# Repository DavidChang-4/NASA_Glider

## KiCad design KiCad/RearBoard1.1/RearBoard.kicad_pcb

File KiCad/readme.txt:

BRGR_schematic is old
BRGRavionics2.4.1 is what we made
See the png for how connectorbit and powerpack interface
Midinterface is how the body connects to the avionics

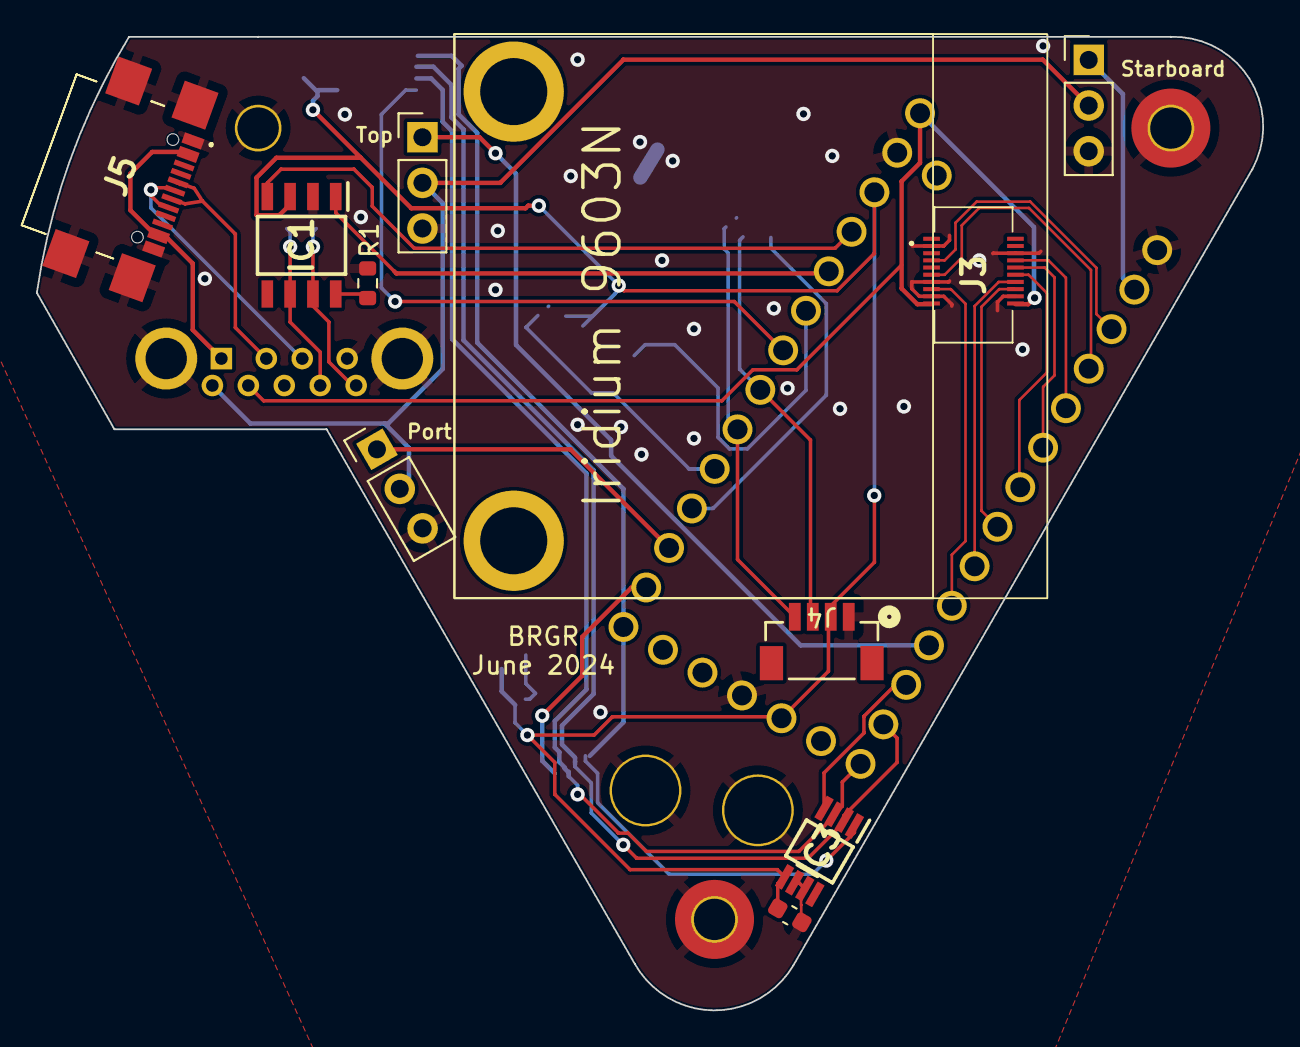
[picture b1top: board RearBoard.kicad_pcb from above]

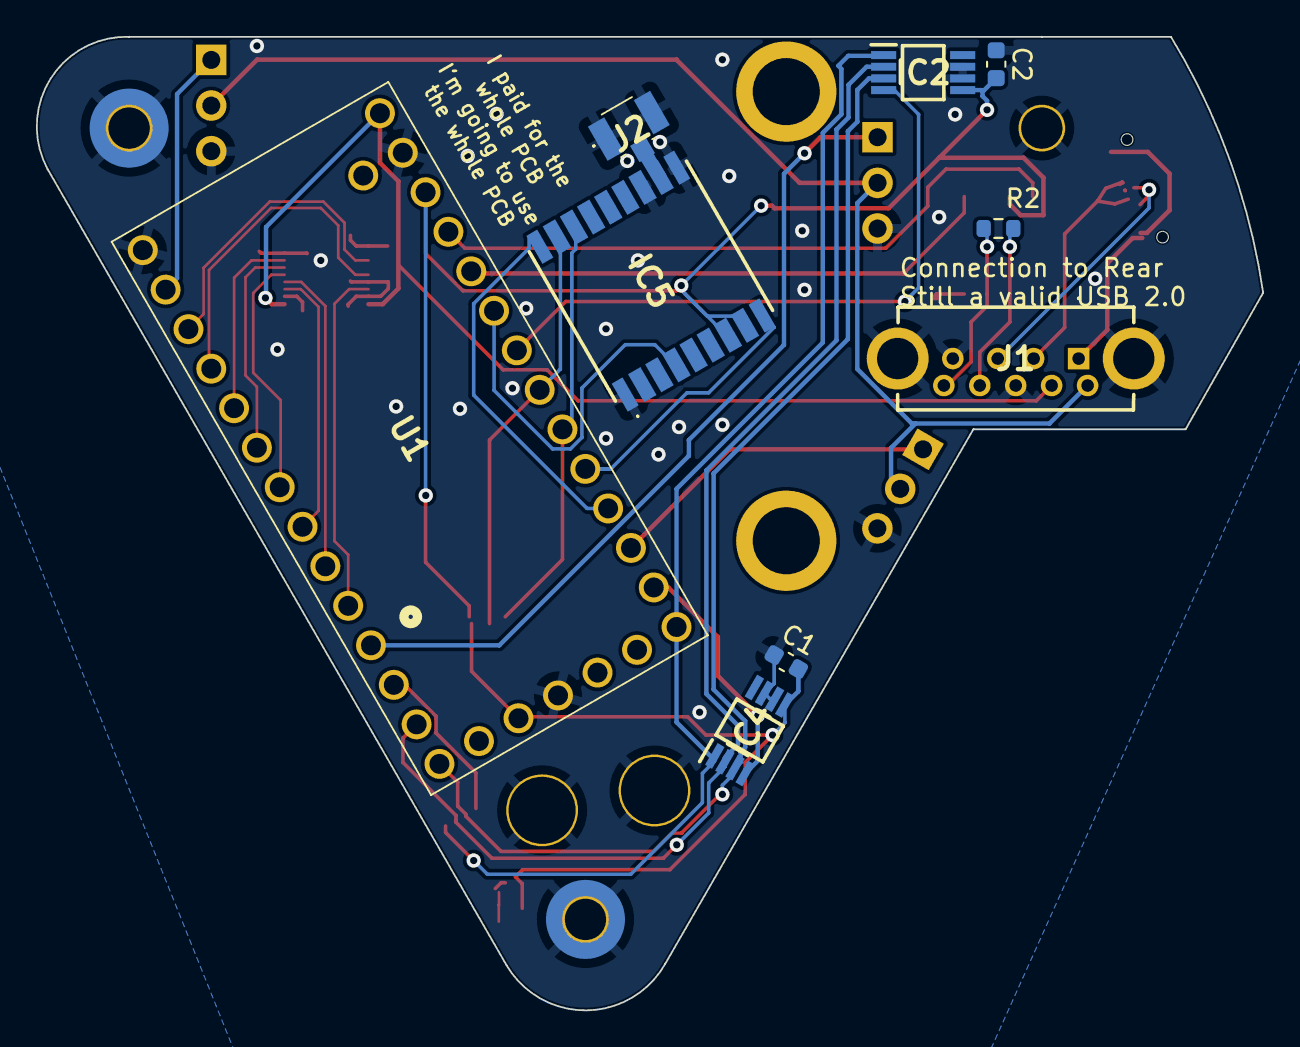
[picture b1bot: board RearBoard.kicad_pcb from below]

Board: 2 copper layers, 68.3 x 54.2 mm, 22 parts (9 on the bottom side), 35 nets.

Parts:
C1, C2, C3: 0.1u; C_0603_1608Metric
H1, H2, H3: MountingHole_Pad; MountingHole_2.2mm_M2_Pad_TopBottom
IC1: SN65HVD230MDREP; SOIC127P600X175-8N
IC2, IC3, IC4: TMAG5170A2QDGKR; SOP65P490X110-8N
IC5: MAX-M10S-00B; MAXM10S00B
J1: SS-52000-004; SS52000004
J2: U.FL-R-SMT_10_; UFLRSMT10
J3: SS4-10-3.00-L-D-K-TR; SS410350LDKTR
J4: BM04B-SRSS-TB; CONN4_BM04B-SRSS_JST
J5: USB4110-GF-A; USB4110GFA
Port: Conn_01x03_Pin; PinHeader_1x03_P2.54mm_Vertical
R1: 10k; R_0603_1608Metric
R2: 120; R_0603_1608Metric
Starboard: Conn_01x03_Pin; PinHeader_1x03_P2.54mm_Vertical
Top: Conn_01x03_Pin; PinHeader_1x03_P2.54mm_Vertical
U1: Teensy4.0; TEENSY40

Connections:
+3.3V: C1.2, C2.2, C3.2, IC1.3 (VCC), IC2.5 (VCC), IC3.5 (VCC), IC4.5 (VCC), IC5.7 (V_IO), IC5.8 (VCC), J4.2, U1.16 (3V3), U1.31 (3V3)
+5V: J1.8 (SSTX-), J3.1, J3.2, U1.33 (VIN)
+BATT: J1.9 (SSTX+), Port.2, Starboard.2, Top.2
/AV USB D+: J1.3 (D+), J5.A6, J5.B6
/AV USB D-: J1.2 (D-), J5.A7, J5.B7
/CAN-H: IC1.7 (CANH), J1.5 (SSRX-), R2.1
/CAN-L: IC1.6 (CANL), J1.6 (SSRX+), R2.2
/CRX: IC1.4 (R), U1.30 (23_A9_CRX1_MCLK1)
/CTS: J3.11, U1.6 (4_BCLK2)
/CTX: IC1.1 (D), U1.29 (22_A8_CTX1)
/DCD: J3.9, U1.7 (5_IN2)
/DSR: J3.10, U1.4 (2_OUT2)
/DTR: J3.14, U1.3 (1_TX1_CTX2_MISO1)
/GPS PPS: IC5.4 (TIMEPULSE), U1.28 (21_A7_RX5_BCLK1)
/GPS Reset: IC5.9 (RESET_N), U1.24 (17_A3_TX4_SDA1)
/GPS Safeboot: IC5.18 (SAFEBOOT_N), U1.23 (16_A2_RX4_SCL1)
/Iridium ON/OFF: J3.5, U1.8 (6_OUT1D)
/Iridium RX: J3.7, U1.9 (7_RX2_OUT1A)
/Iridium TX: J3.6, U1.10 (8_TX2_IN1)
/MISO: IC2.3 (SDO), IC3.3 (SDO), IC4.3 (SDO), U1.14 (12_MISO_MQSL)
/MOSI: IC2.2 (SDI), IC3.2 (SDI), IC4.2 (SDI), U1.13 (11_MOSI_CTX1)
/PortCS: IC3.4 (~CS), U1.12 (10_CS_MQSR)
/PortServo: Port.1, U1.22 (15_A1_RX3_SPDIF_IN)
/RTS: J3.13, U1.5 (3_LRCLK2)
/SCK: IC2.1 (SCK), IC3.1 (SCK), IC4.1 (SCK), U1.20 (13_SCK_CRX1_LED)
/SCL0: IC5.17 (SCL), J4.3, U1.26 (19_A5_SCL0)
/SDA0: IC5.16 (SDA), J4.4, U1.25 (18_A4_SDA0)
/StarboardCS: IC4.4 (~CS), U1.21 (14_A0_TX3_SPDIF_OUT)
/StarboardServo: Starboard.1, U1.2 (0_RX1_CRX2_CS1)
/TopCS: IC2.4 (~CS), U1.27 (20_A6_TX5_LRCLK1)
/TopServo: Top.1, U1.11 (9_OUT1C)
GND: C1.1, C2.1, C3.1, H1.1, H2.1, H3.1, H3.e (1), IC1.2 (GND), IC2.6 (GND), IC2.7 (TEST), IC3.6 (GND), IC3.7 (TEST), IC4.6 (GND), IC4.7 (TEST), IC5.1 (GND_1), IC5.10 (GND_2), IC5.12 (GND_3), J1.4 (GND), J1.7 (GND_DRAIN), J1.MH1, J1.MH2, J2.1 (GND_1), J2.2 (GND_2), J3.3, J3.4, J3.8, J3.15, J3.18, J4.1, J5.A1, J5.A12, J5.B1, J5.B12, J5.MP1, J5.MP2, J5.MP3, J5.MP4, Port.3, R1.2, Starboard.3, Top.3, U1.1 (GND), U1.17 (GND), U1.32 (GND)
unnamed: IC1.8 (RS), R1.1
unnamed: IC5.11 (RF_IN), J2.3 (SIG)
VBUS: J1.1 (VBUS), J5.A4, J5.A9, J5.B4, J5.B9

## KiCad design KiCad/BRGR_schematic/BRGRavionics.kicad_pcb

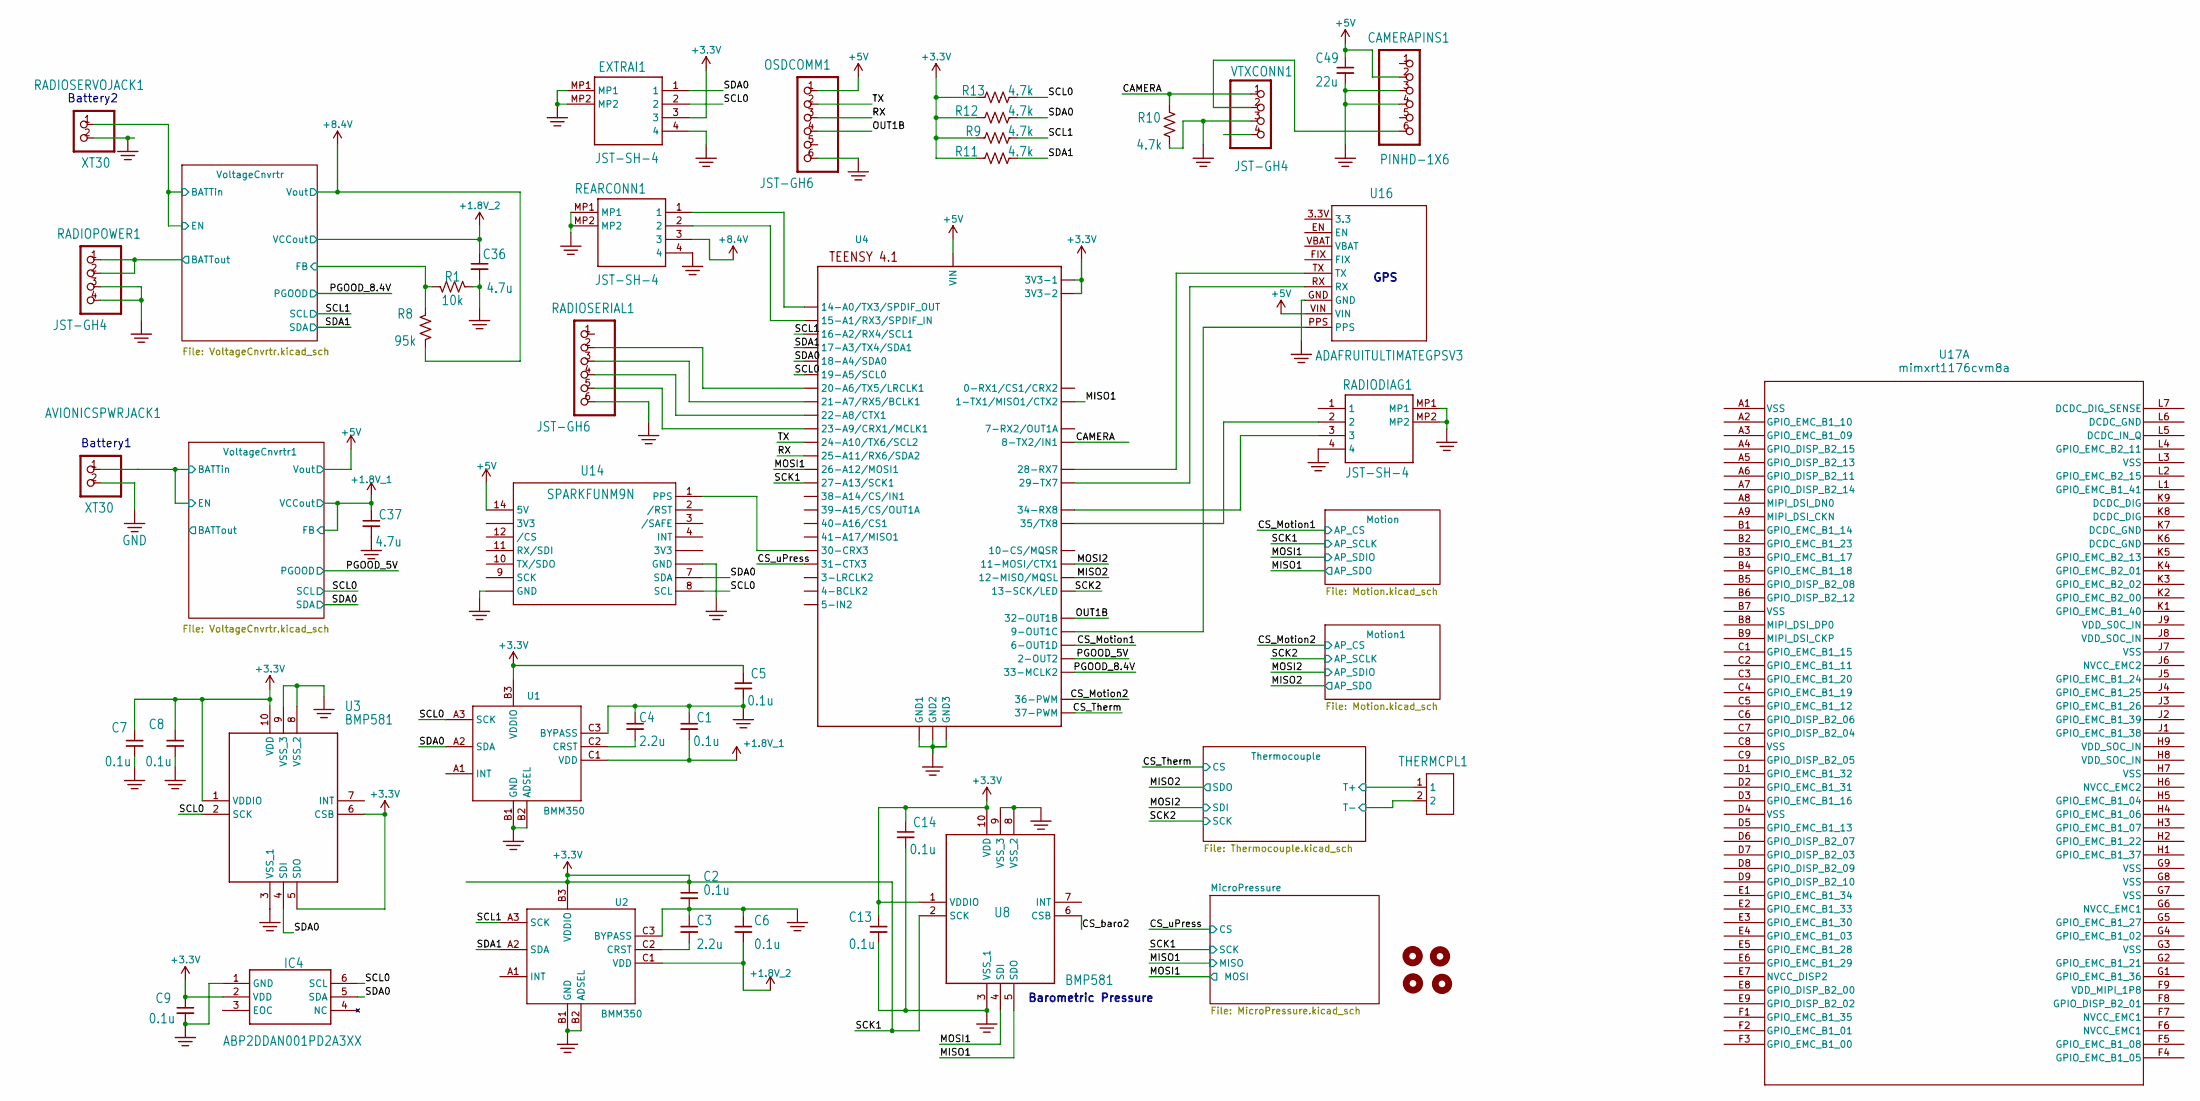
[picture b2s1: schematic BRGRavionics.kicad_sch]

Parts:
AVIONICSPWRJACK1: XT30; AMASS_XT30PW-M
C1, C2, C5, C6, C7, C8, C9, C13, C14: 0.1u; C_0603_1608Metric
C3, C4: 2.2u; C_0603_1608Metric
C36, C37: 4.7u; C_0603_1608Metric
C49: 22u; C_1210_3225Metric
CAMERAPINS1: PINHD-1X6; PinHeader_1x06_P2.54mm_Vertical
EXTRAI1: JST-SH-4; JST_BM04B-SRSS-TB_LF__SN_Mod
H1, H2, H3, H4: MountingHole; MountingHole_70
IC4: ABP2DDAN001PD2A3XX
OSDCOMM1: JST-GH6; JST_SM06B-GHS-TB_LF__SN_Mod
R1: 10k; R_0603_1608Metric
R8: 95k; R_0603_1608Metric
R9, R10, R11, R12, R13: 4.7k; R_0603_1608Metric
RADIODIAG1: JST-SH-4; JST_BM04B-SRSS-TB_LF__SN_Mod
RADIOPOWER1: JST-GH4; JST_SM04B-GHS-TB_LF__SN_-Mod
RADIOSERIAL1: JST-GH6; JST_SM06B-GHS-TB_LF__SN_Mod
RADIOSERVOJACK1: XT30; AMASS_XT30PW-M
REARCONN1: JST-SH-4; JST_SM04B-SRSS-TB(LF)(SN)Mod
THERMCPL1: 2828XX-2282834-2; TerminalBlock_TE_282834-2_1x02_P2.54mm_Horizontal
U1, U2: BMM350; BGA9C40P3X3_128X128X50
U3, U8: BMP581
U4: TEENSY41; MODULE_DEV-16771_v2
U14: SPARKFUNM9N; SparkFun_GPS
U16: ADAFRUITULTIMATEGPSV3; Adafruit_Ultimate_GPS
U17: mimxrt1176cvm8a; 98ASA01216D
VTXCONN1: JST-GH4; JST_BM04B-GHS-TBT(LF)(SN)(N)

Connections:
+5V: C49.1, CAMERAPINS1.2, OSDCOMM1.1, U4.VIN, U14.14 (5V), U16.VIN; also elsewhere on the board
+8V: R8.1, REARCONN1.3; also elsewhere on the board
/CAMERA: R10.2, U4.8 (8-TX2/IN1), VTXCONN1.1
/CS_Motion1: U4.6 (6-OUT1D); also elsewhere on the board
/CS_Motion2: U4.36 (36-PWM); also elsewhere on the board
/CS_Therm: U4.37 (37-PWM); also elsewhere on the board
/CS_uPress: U4.31 (31-CTX3); also elsewhere on the board
/MISO1: U4.1 (1-TX1/MISO1/CTX2), U8.5 (SDO); also elsewhere on the board
/MISO2: U4.12 (12-MISO/MQSL); also elsewhere on the board
/MOSI1: U4.26 (26-A12/MOSI1), U8.4 (SDI); also elsewhere on the board
/MOSI2: U4.11 (11-MOSI/CTX1); also elsewhere on the board
/OUT1B: OSDCOMM1.4, U4.32 (32-OUT1B)
/PGOOD_5V: U4.2 (2-OUT2); also elsewhere on the board
/PGOOD_8.4V: U4.33 (33-MCLK2); also elsewhere on the board
/RX: OSDCOMM1.3, U4.25 (25-A11/RX6/SDA2)
/SCK2: U4.13 (13-SCK/LED); also elsewhere on the board
/SCL0: EXTRAI1.2, R13.1, U1.A3 (SCK), U3.2 (SCK), U4.19 (19-A5/SCL0), U14.8 (SCL); also elsewhere on the board
/SCL1: R9.1, U2.A3 (SCK), U4.16 (16-A2/RX4/SCL1); also elsewhere on the board
/SDA0: EXTRAI1.1, R12.1, U1.A2 (SDA), U3.4 (SDI), U4.18 (18-A4/SDA0), U14.7 (SDA); also elsewhere on the board
/SDA1: R11.1, U2.A2 (SDA), U4.17 (17-A3/TX4/SDA1); also elsewhere on the board
/TX: OSDCOMM1.2, U4.24 (24-A10/TX6/SCL2)
/Thermocouple/T+: THERMCPL1.1; also elsewhere on the board
/Thermocouple/T-: THERMCPL1.2; also elsewhere on the board
/VoltageCnvrtr1/BATTin: AVIONICSPWRJACK1.1 (+); also elsewhere on the board
/VoltageCnvrtr/BATTin: RADIOSERVOJACK1.1 (+); also elsewhere on the board
/VoltageCnvrtr/BATTout: RADIOPOWER1.1, RADIOPOWER1.2; also elsewhere on the board
/VoltageCnvrtr/FB: R1.1, R8.2; also elsewhere on the board
GND: AVIONICSPWRJACK1.2 (-), C1.1, C2.2, C3.1, C4.1, C5.2, C6.1, C7.2, C8.2, C9.2, C13.2, C14.2, C36.2, C37.2, C49.2, CAMERAPINS1.3, CAMERAPINS1.4, EXTRAI1.4, EXTRAI1.MP1, EXTRAI1.MP2, OSDCOMM1.6, R1.2, R10.1, RADIODIAG1.4, RADIODIAG1.MP1, RADIODIAG1.MP2, RADIOPOWER1.3, RADIOPOWER1.4, RADIOSERIAL1.6, RADIOSERVOJACK1.2 (-), REARCONN1.4, REARCONN1.MP1, REARCONN1.MP2, U1.B1 (GND), U1.B2 (ADSEL), U1.C3 (BYPASS), U2.B1 (GND), U2.B2 (ADSEL), U2.C3 (BYPASS), U3.3 (VSS_1), U3.8 (VSS_2), U3.9 (VSS_3), U4.GND1, U4.GND2, U4.GND3, U8.3 (VSS_1), U8.8 (VSS_2), U8.9 (VSS_3), U14.5 (GND), U14.15 (GND), U16.GND, VTXCONN1.3; also elsewhere on the board
unnamed: CAMERAPINS1.6, VTXCONN1.2
unnamed: C4.2, U1.C2 (CRST)
unnamed: C3.2, U2.C2 (CRST)
unnamed: U4.9 (9-OUT1C), U16.PPS
unnamed: REARCONN1.1, U4.14 (14-A0/TX3/SPDIF_OUT)
unnamed: REARCONN1.2, U4.15 (15-A1/RX3/SPDIF_IN)
unnamed: RADIOSERIAL1.2, U4.20 (20-A6/TX5/LRCLK1)
unnamed: RADIOSERIAL1.3, U4.21 (21-A7/RX5/BCLK1)
unnamed: RADIOSERIAL1.4, U4.22 (22-A8/CTX1)
unnamed: RADIOSERIAL1.5, U4.23 (23-A9/CRX1/MCLK1)
unnamed: U4.28 (28-RX7), U16.TX
unnamed: U4.29 (29-TX7), U16.RX
unnamed: RADIODIAG1.3, U4.34 (34-RX8)
unnamed: RADIODIAG1.2, U4.35 (35/TX8)
unnamed: U4.30 (30-CRX3), U14.1 (PPS)

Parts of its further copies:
U5: ABP2DDAN001PD2A3XX

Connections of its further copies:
/SCL0: U5.6 (SCL); also elsewhere on the board
/SDA0: U5.5 (SDA); also elsewhere on the board
GND: U5.1 (GND); also elsewhere on the board

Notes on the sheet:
Barometric Pressure
GPS
Battery2
Battery1

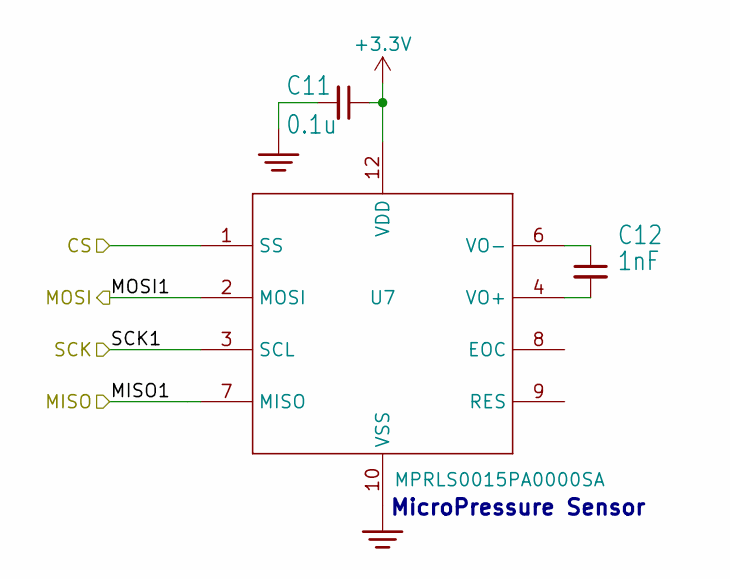
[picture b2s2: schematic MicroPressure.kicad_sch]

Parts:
C11: 0.1u; C_0603_1608Metric
C12: 1nF; C_0603_1608Metric
U7: MPRLS0015PA0000SA

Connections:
/CS_uPress: U7.1 (SS); also elsewhere on the board
/MISO1: U7.7 (MISO); also elsewhere on the board
/MOSI1: U7.2 (MOSI); also elsewhere on the board
GND: C11.2, U7.10 (VSS); also elsewhere on the board
unnamed: C12.2, U7.4 (VO+)
unnamed: C12.1, U7.6 (VO-)

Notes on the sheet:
MicroPressure Sensor

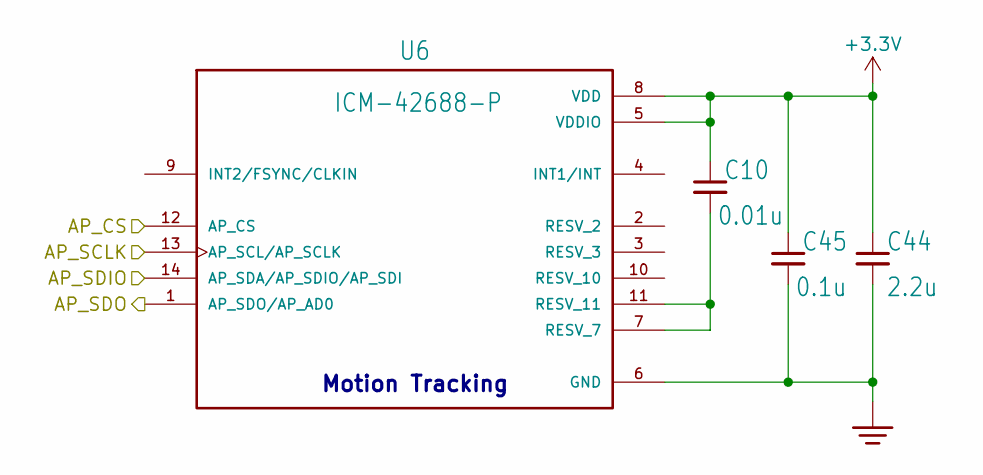
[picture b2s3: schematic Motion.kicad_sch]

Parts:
C10: 0.01u; C_0603_1608Metric
C44: 2.2u; C_0603_1608Metric
C45: 0.1u; C_0603_1608Metric
U6: ICM-42688-P; PQFN50P300X250X97-14N; PARTREV 1.2; DigiKey_Part_Number 1428-ICM-42688-PTR-ND

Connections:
/CS_Motion1: U6.12 (AP_CS); also elsewhere on the board
/MISO1: U6.1 (AP_SDO/AP_AD0); also elsewhere on the board
/MOSI1: U6.14 (AP_SDA/AP_SDIO/AP_SDI); also elsewhere on the board
GND: C44.2, C45.2, U6.6 (GND); also elsewhere on the board
unnamed: C10.2, U6.7 (RESV_7), U6.11 (RESV_11)

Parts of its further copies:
C46: 0.01u; C_0603_1608Metric
C47: 0.1u; C_0603_1608Metric
C48: 2.2u; C_0603_1608Metric
U15: ICM-42688-P; PQFN50P300X250X97-14N; PARTREV 1.2; DigiKey_Part_Number 1428-ICM-42688-PTR-ND

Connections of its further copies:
/CS_Motion2: U15.12 (AP_CS); also elsewhere on the board
/MISO2: U15.1 (AP_SDO/AP_AD0); also elsewhere on the board
/MOSI2: U15.14 (AP_SDA/AP_SDIO/AP_SDI); also elsewhere on the board
/SCK2: U15.13 (AP_SCL/AP_SCLK); also elsewhere on the board
GND: C47.2, C48.2, U15.6 (GND); also elsewhere on the board
unnamed: C46.2, U15.7 (RESV_7), U15.11 (RESV_11)

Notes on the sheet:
Motion Tracking

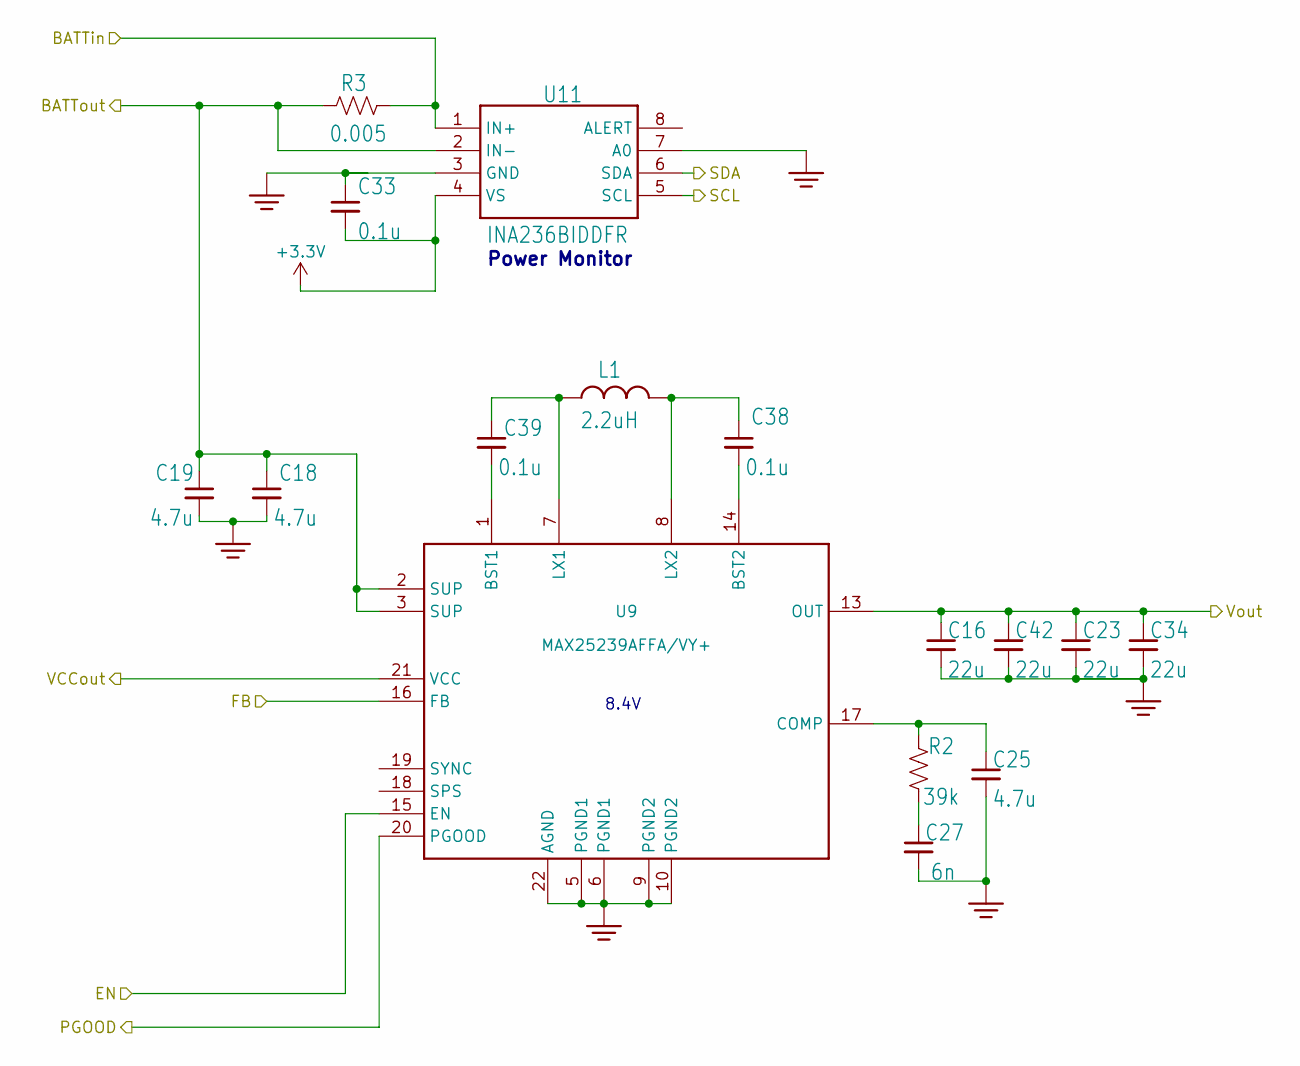
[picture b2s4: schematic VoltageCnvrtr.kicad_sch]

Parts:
C16, C23, C34, C42: 22u; C_1210_3225Metric
C18, C19: 4.7u; C_1206_3216Metric
C25: 4.7u; C_0603_1608Metric
C27: 6n; C_0603_1608Metric
C33, C38, C39: 0.1u; C_0603_1608Metric
L1: 2.2uH; L_Bourns_SRP3020CC
R2: 39k; R_0603_1608Metric
R3: 0.005; RESC6432X55N
U9: MAX25239AFFA/VY+; MAX25239
U11: INA236BIDDFR; SOT23-THN-8

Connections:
+8V: C16.1, C23.1, C34.1, C42.1, U9.12 (OUT), U9.13 (OUT); also elsewhere on the board
/PGOOD_8.4V: U9.20 (PGOOD); also elsewhere on the board
/SCL1: U11.5 (SCL); also elsewhere on the board
/SDA1: U11.6 (SDA); also elsewhere on the board
/VoltageCnvrtr/BATTin: R3.1, U9.15 (EN), U11.1 (IN+); also elsewhere on the board
/VoltageCnvrtr/BATTout: C18.1, C19.1, R3.2, U9.2 (SUP), U9.3 (SUP), U11.2 (IN-); also elsewhere on the board
/VoltageCnvrtr/FB: U9.16 (FB); also elsewhere on the board
GND: C16.2, C18.2, C19.2, C23.2, C25.2, C27.2, C33.1, C34.2, C42.2, U9.5 (PGND1), U9.6 (PGND1), U9.9 (PGND2), U9.10 (PGND2), U9.22 (AGND), U11.3 (GND), U11.7 (A0); also elsewhere on the board
unnamed: C27.1, R2.2
unnamed: C39.2, U9.1 (BST1)
unnamed: C38.2, U9.14 (BST2)
unnamed: C25.1, R2.1, U9.17 (COMP)
unnamed: C39.1, L1.1, U9.7 (LX1)
unnamed: C38.1, L1.2, U9.8 (LX2)

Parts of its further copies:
C17, C24, C35, C43: 22u; C_1210_3225Metric
C20, C21: 4.7u; C_1206_3216Metric
C26: 4.7u; C_0603_1608Metric
C28: 6n; C_0603_1608Metric
C32, C40, C41: 0.1u; C_0603_1608Metric
L2: 2.2uH; L_Bourns_SRP3020CC
R4: 39k; R_0603_1608Metric
R5: 0.005; RESC6432X55N
U10: MAX25239AFFA/VY+; MAX25239
U12: INA236BIDDFR; SOT23-THN-8

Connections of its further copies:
+5V: C17.1, C24.1, C35.1, C43.1, U10.12 (OUT), U10.13 (OUT); also elsewhere on the board
/PGOOD_5V: U10.20 (PGOOD); also elsewhere on the board
/SCL0: U12.5 (SCL); also elsewhere on the board
/SDA0: U12.6 (SDA); also elsewhere on the board
/VoltageCnvrtr1/BATTin: R5.1, U10.15 (EN), U12.1 (IN+); also elsewhere on the board
/VoltageCnvrtr1/BATTout: C20.1, C21.1, R5.2, U10.2 (SUP), U10.3 (SUP), U12.2 (IN-)
GND: C17.2, C20.2, C21.2, C24.2, C26.2, C28.2, C32.1, C35.2, C43.2, U10.5 (PGND1), U10.6 (PGND1), U10.9 (PGND2), U10.10 (PGND2), U10.22 (AGND), U12.3 (GND), U12.7 (A0); also elsewhere on the board
unnamed: C28.1, R4.2
unnamed: C41.2, U10.1 (BST1)
unnamed: C40.2, U10.14 (BST2)
unnamed: C26.1, R4.1, U10.17 (COMP)
unnamed: C41.1, L2.1, U10.7 (LX1)
unnamed: C40.1, L2.2, U10.8 (LX2)

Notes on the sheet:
Power Monitor
8.4V

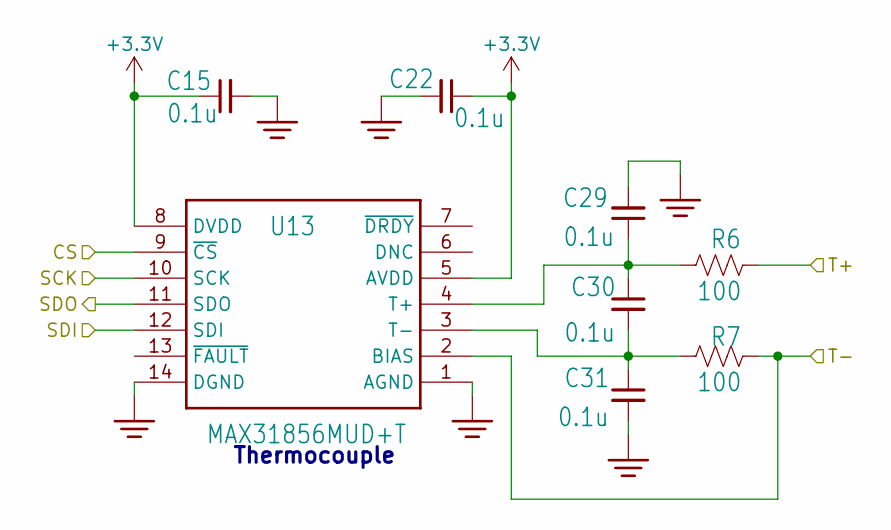
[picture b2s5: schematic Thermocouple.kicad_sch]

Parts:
C15, C22, C29, C30, C31: 0.1u; C_0603_1608Metric
R6, R7: 100; R_0603_1608Metric
U13: MAX31856MUD+T; SOP65P640X110-14N

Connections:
/CS_Therm: U13.9 (~CS); also elsewhere on the board
/MISO2: U13.11 (SDO); also elsewhere on the board
/MOSI2: U13.12 (SDI); also elsewhere on the board
/SCK2: U13.10 (SCK); also elsewhere on the board
/Thermocouple/T+: R6.1; also elsewhere on the board
/Thermocouple/T-: R7.1, U13.2 (BIAS); also elsewhere on the board
GND: C15.2, C22.2, C29.2, C31.2, U13.1 (AGND), U13.14 (DGND); also elsewhere on the board
unnamed: C29.1, C30.1, R6.2, U13.4 (T+)
unnamed: C30.2, C31.1, R7.2, U13.3 (T-)

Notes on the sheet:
Thermocouple

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
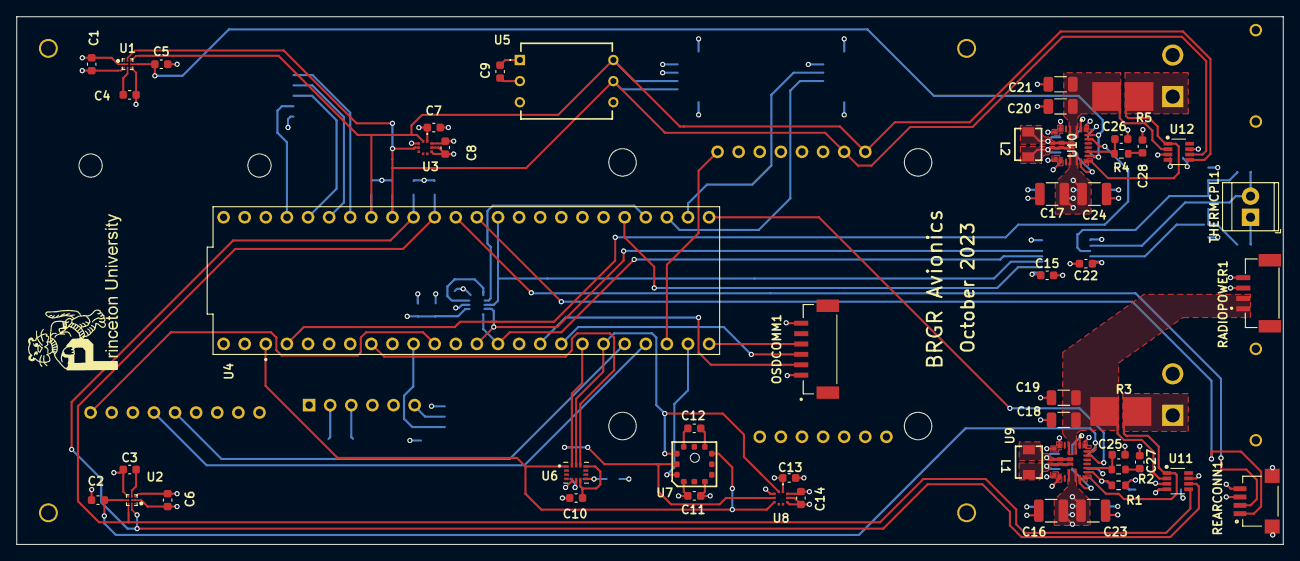
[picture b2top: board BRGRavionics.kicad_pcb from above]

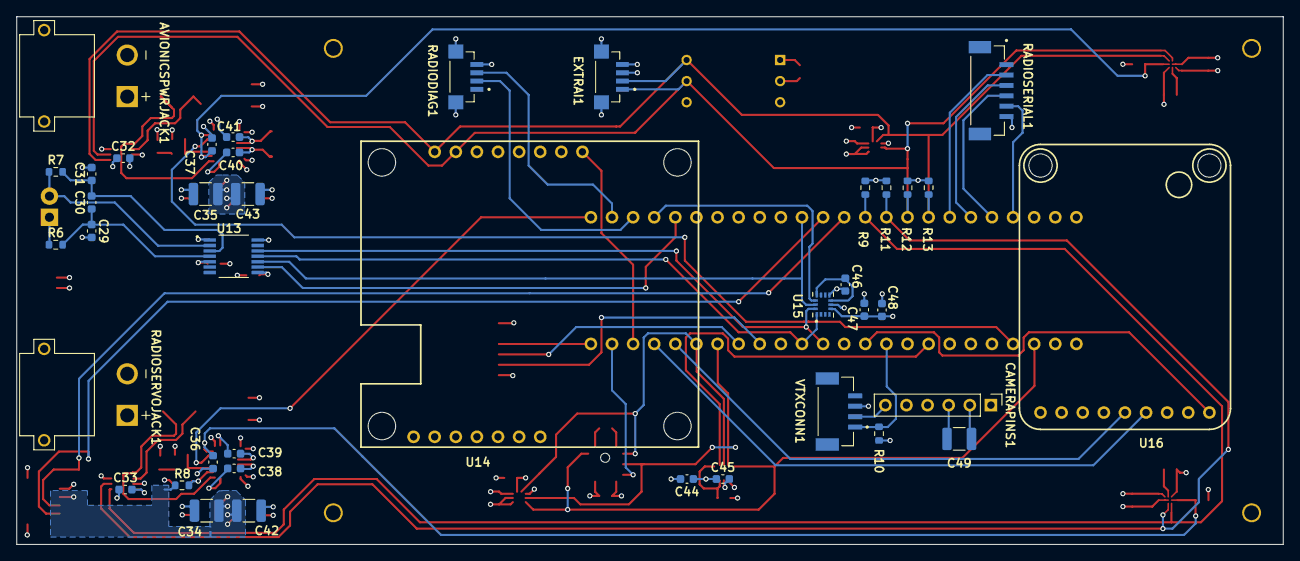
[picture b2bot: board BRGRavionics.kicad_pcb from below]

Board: 4 copper layers, 152.4 x 63.5 mm, 96 parts (40 on the bottom side), 66 nets.

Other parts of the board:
G1: LOGO; t_

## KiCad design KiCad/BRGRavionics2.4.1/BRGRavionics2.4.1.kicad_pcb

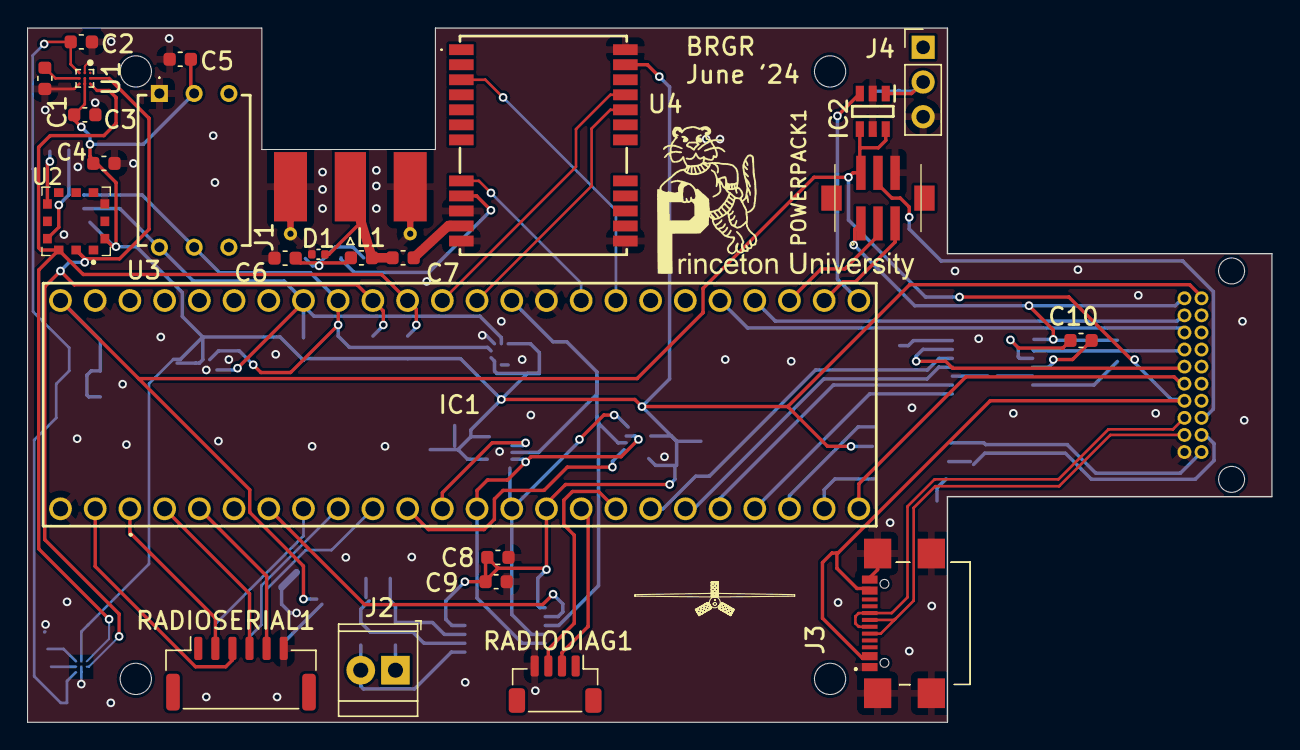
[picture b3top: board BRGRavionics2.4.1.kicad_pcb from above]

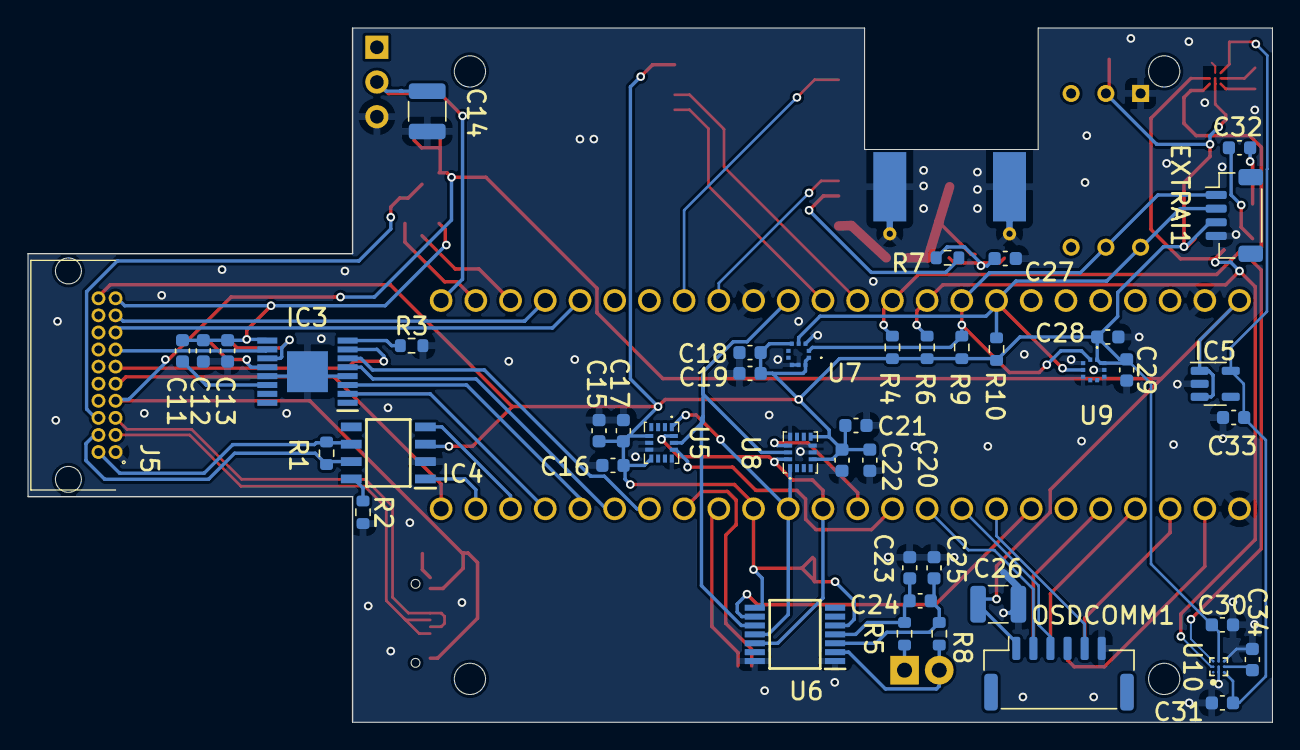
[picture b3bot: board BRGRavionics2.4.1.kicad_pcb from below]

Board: 2 copper layers, 91.1 x 50.8 mm, 76 parts (46 on the bottom side), 65 nets.

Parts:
C1, C16, C22, C34: 2.2u; C_0603_1608Metric
C2, C3, C4, C5, C8, C9, C10, C11, C12, C17, C18, C19, C20, C23, C24, C25, C28, C29, C30, C31, C33: 0.1u; C_0603_1608Metric
C6: 0.1uF; C_0603_1608Metric
C7, C27: 47pF; C_0603_1608Metric
C13: 100u; C_0603_1608Metric
C14, C26: 22u; C_1210_3225Metric
C15, C21: 0.01u; C_0603_1608Metric
C32: 1nF; C_0603_1608Metric
D1: TVS_0402; C_0402_1005Metric
EXTRAI1: JST-SH-4; JST_SH_BM04B-SRSS-TB_1x04-1MP_P1.00mm_Vertical
G1: LOGO; t_
H1, H2, H3, H4: MountingHole; MountingHole_90
IC1: TEENSY_4.1; TEENSY41
IC2: AP22913W6-7; SOT95P285X140-6N
IC3: DRV8800PWPR; SOP65P640X120-17N
IC4: SN65HVD230MDREP; SOIC127P600X175-8N
IC5: ADP151WAUJZ-1.8-R7; TSOT-23-5
J1: SMA_EdgeMount; SMA_Molex_73251-1153_EdgeMount_Horizontal
J2: Thermocouple Terminal; TerminalBlock_TE_282834-2_1x02_P2.54mm_Horizontal
J3: USB4110-GF-A; USB4110GFA
J4: Camera Pins; PinHeader_1x03_P2.54mm_Vertical
J5: G125-MH12005L5P
L1: 33nH; C_0603_1608Metric
OSDCOMM1: JST-GH6; JST_GH_SM06B-GHS-TB_1x06-1MP_P1.25mm_Horizontal
POWERPACK1: G125-MS10605L3P
R1: 120; R_0603_1608Metric
R2: 10k; R_0603_1608Metric
R3: 0.2; R_0603_1608Metric
R4, R6, R9, R10: 4.7k; R_0603_1608Metric
R5, R8: 100; R_0603_1608Metric
R7: 10; R_0603_1608Metric
RADIODIAG1: JST-SH-4; JST_SH_BM04B-SRSS-TB_1x04-1MP_P1.00mm_Vertical
RADIOSERIAL1: JST-GH6; JST_GH_SM06B-GHS-TB_1x06-1MP_P1.25mm_Horizontal
U1, U10: BMM350; BGA9C40P3X3_128X128X50
U2: MPRLS0015PA0000SA; MPRLS0025PA00001A
U3: ABP2DDAN001PD2A3XX; ABP2DANT001BA2A3XX
U4: NEO-M10N; NEOM9N00B
U5, U8: ICM-42688-P; IIM42352
U6: MAX31856MUD+T; SOP65P640X110-14N
U7, U9: BMP581

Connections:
+1V8_1: C2.2, C31.2, C33.1, IC5.5 (VOUT), U1.C1 (VDD), U10.C1 (VDD)
+3.3V: C3.1, C4.1, C5.1, C8.1, C9.1, C15.1, C16.1, C17.1, C18.1, C19.1, C20.1, C21.1, C22.1, C28.1, C29.1, C30.1, EXTRAI1.3, IC1.42 (3.3V_1), IC4.3 (VCC), J5.20, R4.2, R6.2, R9.2, R10.2, U1.B2 (ADSEL), U1.B3 (VDDIO), U2.12 (VDD), U3.2 (VDD), U4.23 (VCC), U5.5 (VDDIO), U5.8 (VDD), U6.5 (AVDD), U6.8 (DVDD), U7.1 (VDDIO), U7.5 (SDO), U7.10 (VDD), U8.5 (VDDIO), U8.8 (VDD), U9.1 (VDDIO), U9.10 (VDD), U10.B3 (VDDIO)
+5V: C26.1, IC1.55 (VIN_(3.6_TO_5.5_VOLTS)), IC2.4 (VIN_1), IC2.6 (VIN_2), IC5.1 (VIN), IC5.3 (EN), J3.A4, J3.A9, J3.B4, J3.B9, J5.4, OSDCOMM1.1, POWERPACK1.4
+BATT: C11.2, C12.1, C13.1, IC3.9 (VBB), J5.10, POWERPACK1.1
/CAN-H: IC4.7 (CANH), J5.12, R1.1
/CAN-L: IC4.6 (CANL), J5.11, R1.2
/CRX: IC1.30 (CRX3), IC4.4 (R)
/CS_Motion1: IC1.9 (OUT1C), U5.12 (AP_CS)
/CS_Motion2: IC1.10 (CS_1), U8.12 (AP_CS)
/CS_Therm: IC1.5 (IN2), U6.9 (~CS)
/CTX: IC1.31 (CTX3), IC4.1 (D)
/CameraON: IC1.33 (MCLK2), IC2.3 (ON)
/Encoder A: IC1.37 (CS_3), J5.8
/Encoder B: IC1.36 (CS_2), J5.9
/GPS Pulse: IC1.40 (A16), U4.3 (TIME_PULSE)
/GPS RESET: IC1.41 (A17), U4.8 (RESET_N)
/GPS RX: IC1.14 (A0), U4.20 (TXD)
/GPS TX: IC1.15 (A1), U4.21 (RXD)
/Limit Switch: IC1.32 (OUT1B), J5.5
/M+: IC3.7 (OUT+), J5.6
/M-: IC3.10 (OUT-), J5.7
/MISO1: IC1.12 (MISO), U5.1 (AP_SDO/AP_AD0), U6.11 (SDO), U8.1 (AP_SDO/AP_AD0)
/MOSI1: IC1.11 (MOSI), U5.14 (AP_SDA/AP_SDIO/AP_SDI), U6.12 (SDI), U8.14 (AP_SDA/AP_SDIO/AP_SDI)
/Motor Enable: IC1.28 (RX7), IC3.3 (PHASE)
/Motor Mode: IC1.29 (TX7), IC3.2 (MODE)
/Motor Phase: IC1.26 (A12), IC3.6 (ENABLE)
/Motor Sleep: IC1.27 (A13), IC3.5 (NSLEEP)
/OSD DTR: IC1.6 (OUT1D), OSDCOMM1.5
/OSD RX: IC1.7 (RX2), OSDCOMM1.3
/OSD TX: IC1.8 (TX2), OSDCOMM1.2
/PowerRX: IC1.34 (RX8), POWERPACK1.3
/PowerTX: IC1.35 (TX8), POWERPACK1.2
/RADIO CTS: IC1.2 (OUT2), RADIOSERIAL1.4
/RADIO RTS: IC1.3 (LRCLK2), RADIOSERIAL1.5
/RADIO RX: IC1.57 (RX1), RADIOSERIAL1.3
/RADIO TX: IC1.1 (TX1), RADIOSERIAL1.2
/SCK1: IC1.13 (SCK), U5.13 (AP_SCL/AP_SCLK), U6.10 (SCK), U8.13 (AP_SCL/AP_SCLK)
/SCL0: EXTRAI1.2, IC1.19 (A5), R10.1, U3.6 (SCL), U7.4 (SDI), U9.4 (SDI)
/SCL1: IC1.16 (A2), R4.1, U1.A3 (SCK), U2.3 (SCL), U10.A3 (SCK)
/SDA0: EXTRAI1.1, IC1.18 (A4), R9.1, U3.5 (SDA), U7.2 (SCK), U9.2 (SCK)
/SDA1: IC1.17 (A3), R6.1, U1.A2 (SDA), U2.2 (MOSI), U10.A2 (SDA)
/Thermocouple/T+: J2.1, R5.1
/Thermocouple/T-: J2.2, R8.1, U6.2 (BIAS)
/USB D+: J3.A6, J3.B6, J5.3
/USB D-: J3.A7, J3.B7, J5.2
GND: C1.1, C2.1, C3.2, C4.2, C5.2, C6.2, C8.2, C9.2, C12.2, C13.2, C14.2, C15.2, C16.2, C17.2, C18.2, C19.2, C20.2, C21.2, C22.2, C23.2, C25.2, C26.2, C27.2, C28.2, C29.2, C30.2, C31.1, C33.2, C34.1, D1.1 (A1), EXTRAI1.4, IC1.69 (GND_4), IC1.70 (GND_5), IC1.71 (GND_6), IC2.2 (GND_1), IC2.5 (GND_2), IC3.4 (GND_1), IC3.13 (GND_2), IC4.2 (GND), IC5.2 (GND), J1.2 (1), J3.A1, J3.A12, J3.B1, J3.B12, J3.MP1, J3.MP2, J3.MP3, J3.MP4, J4.3, J5.1, OSDCOMM1.6, POWERPACK1.6, R2.2, R3.2, RADIODIAG1.4, RADIOSERIAL1.6, U1.B1 (GND), U1.C3 (BYPASS), U2.10 (VSS), U3.1 (GND), U4.10 (GND_4), U4.12 (GND_3), U4.13 (GND_1), U4.24 (GND_2), U5.6 (GND), U5.7 (RESV_7), U5.11 (RESV_11), U6.1 (AGND), U6.14 (DGND), U7.3 (VSS_1), U7.8 (VSS_2), U7.9 (VSS_3), U8.6 (GND), U8.7 (RESV_7), U8.11 (RESV_11), U9.3 (VSS_1), U9.5 (SDO), U9.8 (VSS_2), U9.9 (VSS_3), U10.B1 (GND), U10.B2 (ADSEL), U10.C3 (BYPASS)
unnamed: C6.1, C27.1, L1.1, R7.1
unnamed: C7.1, D1.2 (A2), J1.1 (SIG), L1.2
unnamed: IC4.8 (RS), R2.1
unnamed: C10.2, IC3.11 (CP1)
unnamed: C10.1, IC3.12 (CP2)
unnamed: IC3.8 (SENSE), R3.1
unnamed: C11.1, IC3.14 (VCP)
unnamed: C14.1, IC2.1 (OUT), J4.2
unnamed: IC1.24 (A10), RADIODIAG1.2
unnamed: IC1.25 (A11), RADIODIAG1.3
unnamed: C1.2, U1.C2 (CRST)
unnamed: C32.2, U2.4 (VO+)
unnamed: C32.1, U2.6 (VO-)
unnamed: C7.2, U4.11 (RF_IN)
unnamed: R7.2, U4.9 (VCC_RF)
unnamed: C23.1, C24.1, R5.2, U6.4 (T+)
unnamed: C24.2, C25.1, R8.2, U6.3 (T-)
unnamed: C34.2, U10.C2 (CRST)
VBUS: J5.13, POWERPACK1.5
